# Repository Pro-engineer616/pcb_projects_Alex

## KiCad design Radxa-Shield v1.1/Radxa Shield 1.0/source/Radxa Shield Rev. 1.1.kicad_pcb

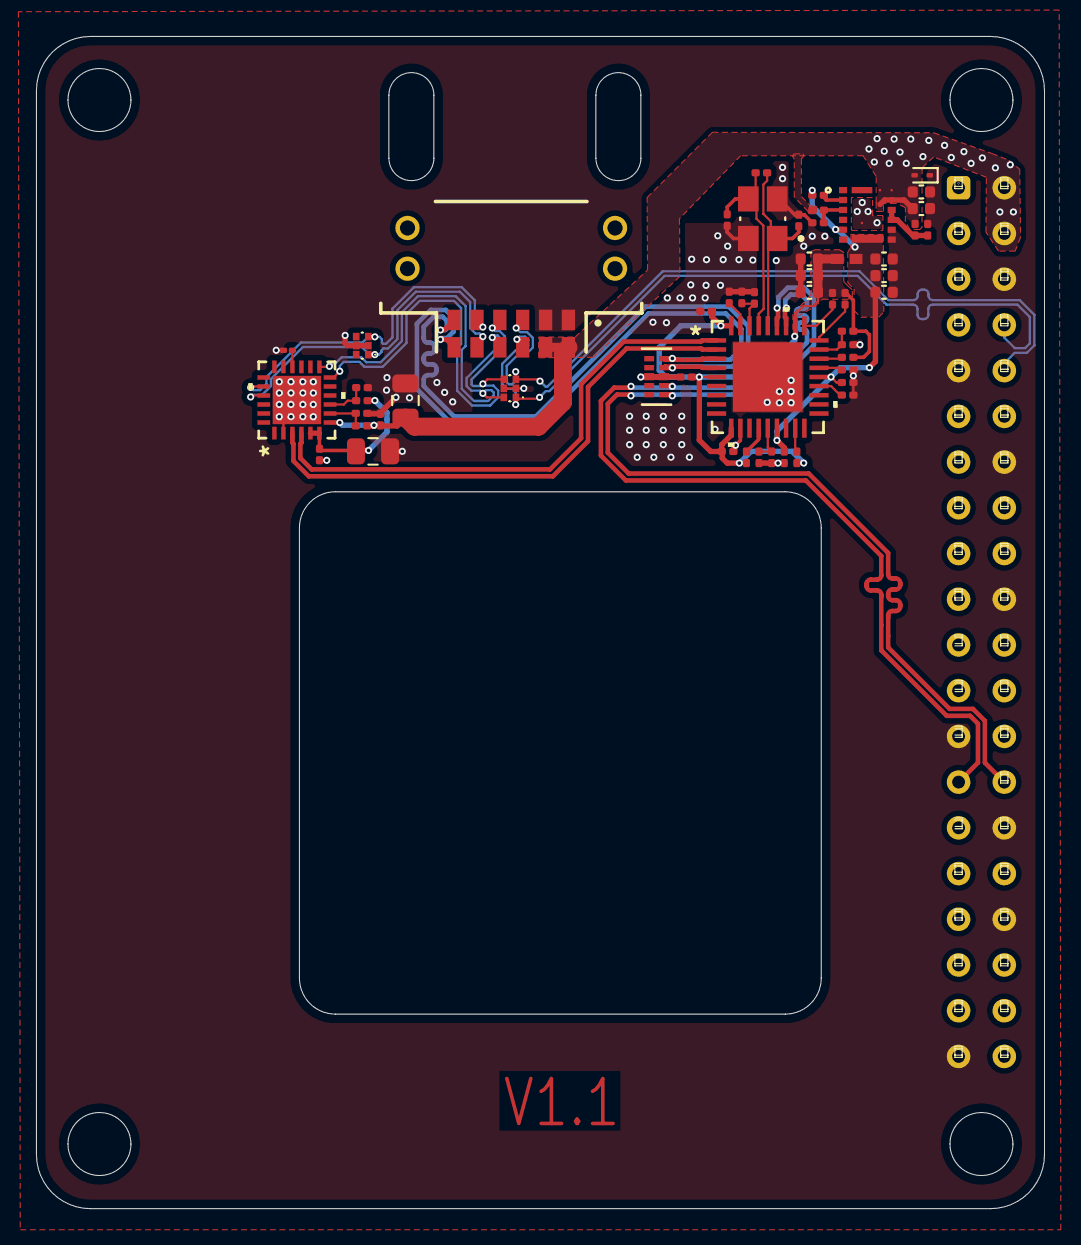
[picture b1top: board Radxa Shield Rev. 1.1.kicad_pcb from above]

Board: 2 copper layers, 56.0 x 65.1 mm, 55 parts (1 on the bottom side), 36 nets.

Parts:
C1, C3, C5, C8, C11, C16, C18, C19, C21, C22, C23: 100n; C_0201_0603Metric
C2, C4: 10u; C_0805_2012Metric
C6: 4.7u; C_01005_0402Metric
C7, C9, C10: 22uF; C_0402_1005Metric
C12, C17: 10nF; C_0201_0603Metric
C13: 220n; C_0201_0603Metric
C14, C15: 18p; C_0201_0603Metric
C24, C25, C26, C27, C28: 10uF; C_0402_1005Metric
D1, D2: PESD3V3L4UF,115; PESD3V3L5UF115
D3: ESD9B5.0ST5G; D_SOD-923
D4: TPD4EUSB30DQAR; DQA10
J1: Conn_02x10_Odd_Even; Samtec_HLE-120-02-xx-DV-TE_2x20_P2.54mm_Horizontal
J2: TFM-106-02-L-DH-TR; SAMTEC_TFM-106-02-L-DH-TR
L1: BLM15BB221SN1D; IND_BLM15_0402_MUR
R1: 24k; R_0201_0603Metric
R2: 47k; R_0201_0603Metric
R3: 4.3k; R_0201_0603Metric
R4, R9, R10, R11, R13, R16, R17: 10k; R_0201_0603Metric
R5: 20k; R_0201_0603Metric
R6: 49.9k; R_0201_0603Metric
R7: 2.7R; R_0201_0603Metric
R8: 12k; R_0201_0603Metric
R12, R14: 100k; R_0201_0603Metric
R15: 1M; R_0201_0603Metric
U1: CP2105-F01-GM; QFN24_4X4_SIL-L
U2: USB2512BI-AEZG; QFN36_6X6MC_MCH
U3: FS1703-3300-AS; P11F1_TDK
Y1: 24MHz; XTAL_TSX-3225_40.0000MF20X-K0

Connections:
+3V3: C7.1, C18.2, C19.2, C24.1, C25.1, L1.2, R6.1, U2.15 (VDD33), U2.23 (VDD33), U3.5 (VOS), U3.7 (VOUT)
+5V: C3.1, C4.1, C9.1, C10.1, D3.2 (A2), J1.2, J1.4, J2.02, J2.04, R1.1, R4.1, R7.1, U1.7 (REGIN), U3.12 (PVIN), U3.13 (PVIN), U3.14 (PVIN), U3.17 (PVIN)
+VDDA33: C21.2, C22.2, C23.2, C26.1, C27.1, C28.1, L1.1, R9.1, R10.1, R11.1, R14.1, R16.2, R17.2, U2.5 (VDDA33), U2.10 (VDDA33), U2.29 (VDDA33), U2.36 (VDDA33)
D+: D4.4 (D2+), J2.11, U2.4 (USBDP_DN2/PRT_DIS_P2)
D-: D4.5 (D2-), J2.12, U2.3 (USBDM_DN2/PRT_DIS_M2)
GND: C1.2, C2.2, C3.2, C4.2, C5.2, C6.2, C7.2, C8.2, C9.2, C10.2, C11.1, C12.1, C13.2, C14.2, C15.2, C16.1, C17.1, C18.1, C19.1, C21.1, C22.1, C23.1, C24.2, C25.2, C26.2, C27.2, C28.2, D1.2 (common_anode_1), D1.5 (common_anode_2), D2.2 (common_anode_1), D2.5 (common_anode_2), D3.1 (A1), D4.3 (GND), D4.8 (GND), J1.6, J1.9, J1.14, J1.20, J1.25, J1.30, J1.34, J1.39, J2.01, J2.03, R2.1, R5.2, R8.2, R12.1, R13.1, U1.2 (GND), U1.25 (EPAD), U2.11 (TEST), U2.37 (EPAD), U3.8 (PGND), U3.9 (AGND), U3.16 (PGND), Y1.2 (GND), Y1.4 (GND__1)
unnamed: C5.1, R3.2, U1.9 (*RST)
unnamed: C6.1, U1.16 (NC/DCD_ECI/VPP)
unnamed: R1.2, R2.2, U1.8 (VBUS)
unnamed: C16.2, C17.2, U2.14 (CRFILT)
unnamed: R11.2, U2.25 (HS_IND/CFG_SEL1)
unnamed: R16.1, U2.13 (OCS_N1)
unnamed: R17.1, U2.17 (OCS_N2)
unnamed: C11.2, C12.2, U2.34 (PLLFILT)
unnamed: R8.1, U2.35 (RBIAS)
unnamed: C13.1, R14.2, U2.26 (RESET_N)
unnamed: R12.2, U2.24 (SCL/SMBCLK/CFG_SEL0)
unnamed: R13.2, U2.22 (SDA/SMBDATA/NON_REM1)
unnamed: R9.2, U2.28 (SUSP_IND/LOCAL_PWR/NON_REM0)
unnamed: R10.2, U2.27 (VBUS_DET)
unnamed: R4.2, R5.1, U3.3 (EN)
unnamed: C8.1, R7.2, U3.10 (VCC), U3.11 (VIN)
PG: R6.2, U3.2 (PG)
UART_RX_ELRS: D1.3 (cathode_(diode_2)), J1.10, J2.05
UART_RX_FC: D1.4 (cathode_(diode_3)), J2.07, U1.12 (RXD_ECI)
UART_RX_HALOW: D2.3 (cathode_(diode_2)), J2.09, U1.20 (RXD_SCI)
UART_TX_ELRS: D1.1 (cathode_(diode_1)), J1.8, J2.06
UART_TX_FC: D1.6 (cathode_(diode_4)), J2.08, U1.13 (TXD_ECI)
UART_TX_HALOW: D2.1 (cathode_(diode_1)), J2.10, U1.21 (TXD_SCI)
USB1_N: U1.4 (D-), U2.1 (USBDM_DN1/PRT_DIS_M1)
USB1_P: U1.3 (D+), U2.2 (USBDP_DN1/PRT_DIS_P1)
USB DN: D4.2 (D1-), J1.27, U2.30 (USBDM_UP)
USB DP: D4.1 (D1+), J1.28, U2.31 (USBDP_UP)
VDD: C1.1, C2.1, R3.1, U1.5 (VIO), U1.6 (VDD)
XTALIN: C15.1, R15.1, U2.33 (XTALIN/CLKIN), Y1.3
XTALOUT: C14.1, R15.2, U2.32 (XTALOUT), Y1.1

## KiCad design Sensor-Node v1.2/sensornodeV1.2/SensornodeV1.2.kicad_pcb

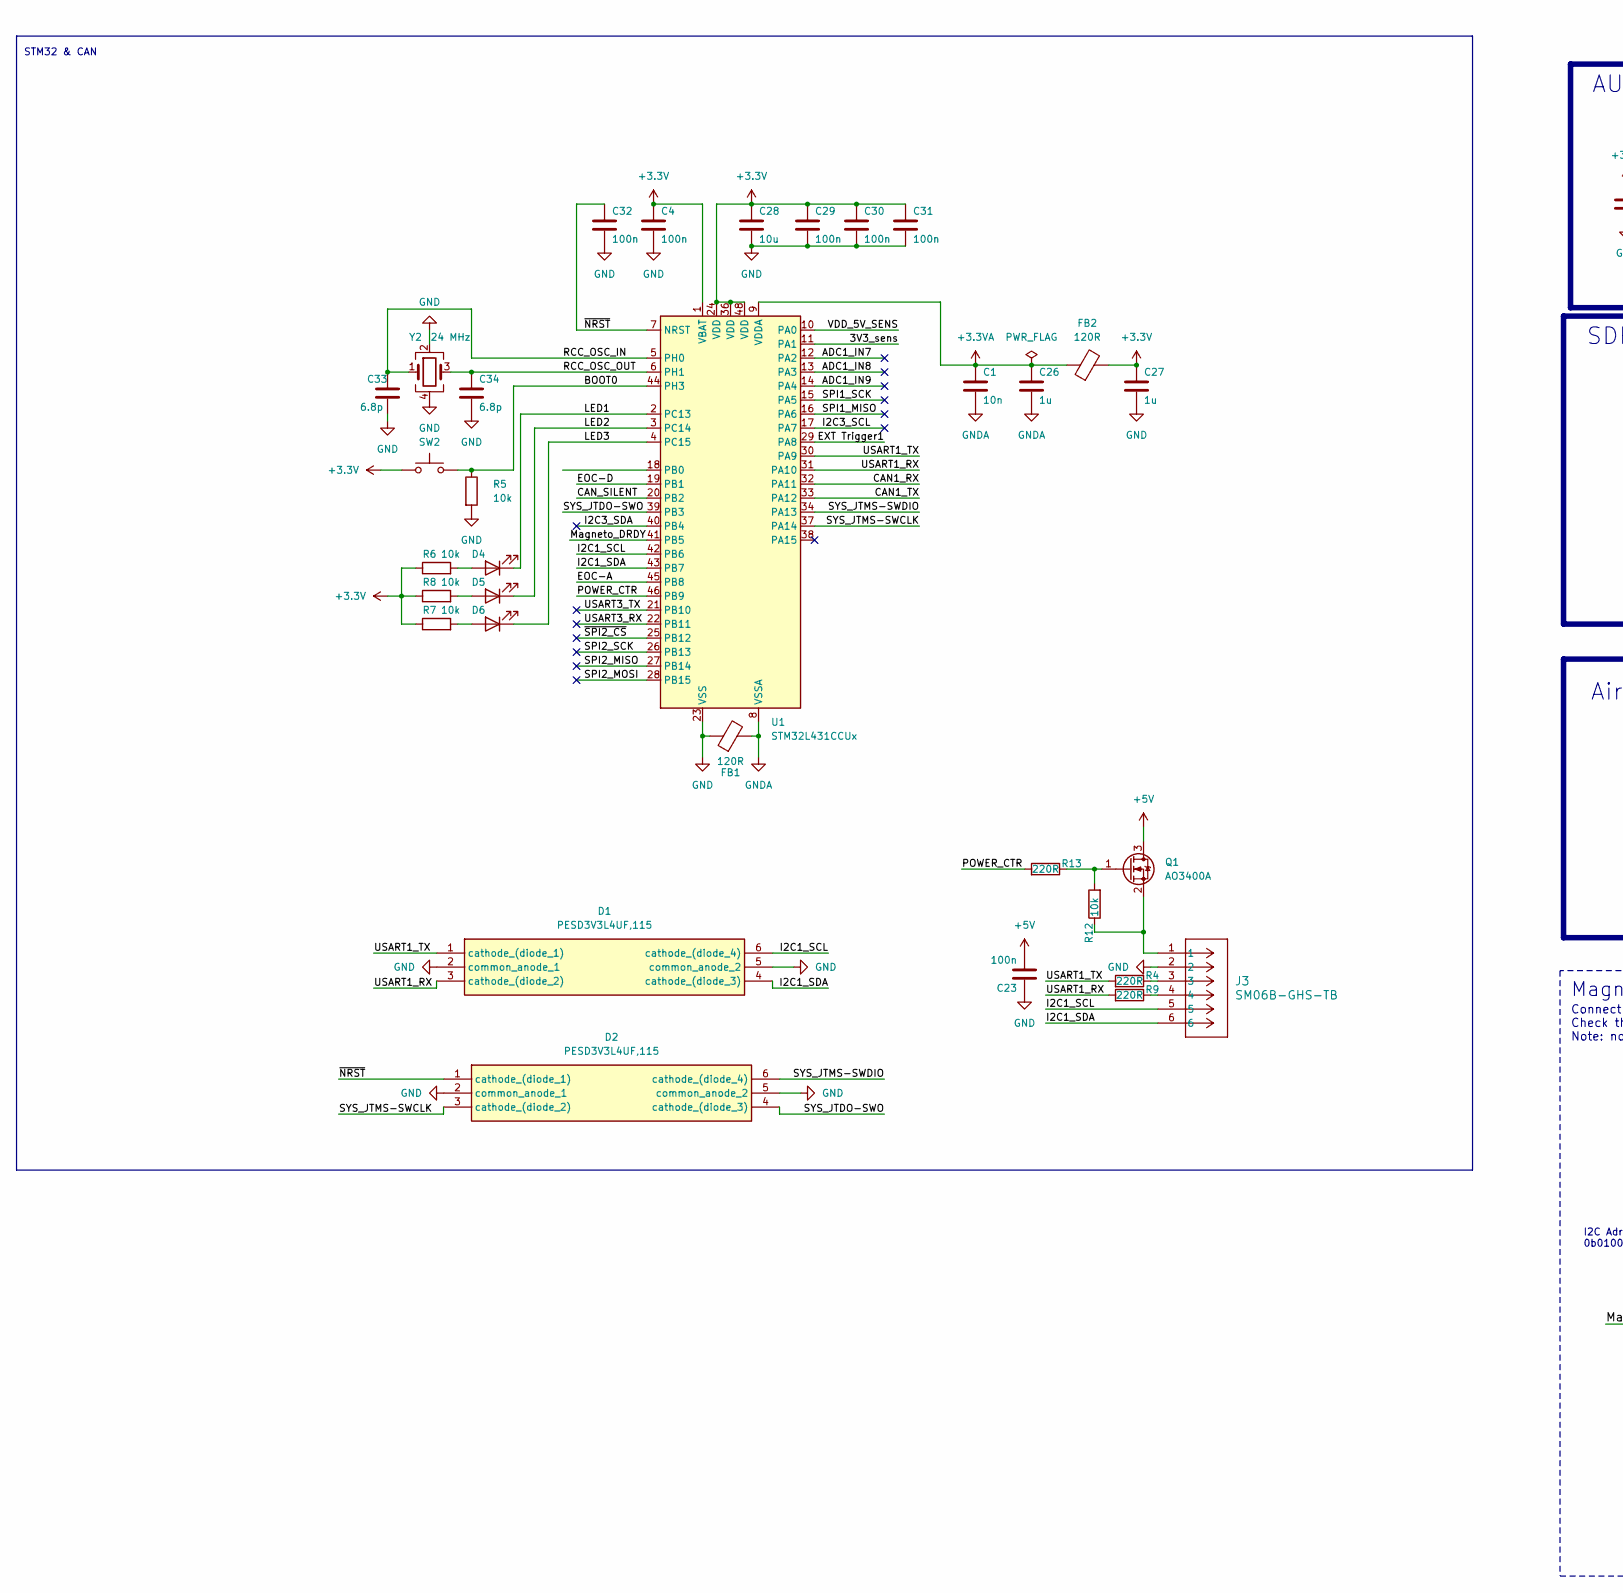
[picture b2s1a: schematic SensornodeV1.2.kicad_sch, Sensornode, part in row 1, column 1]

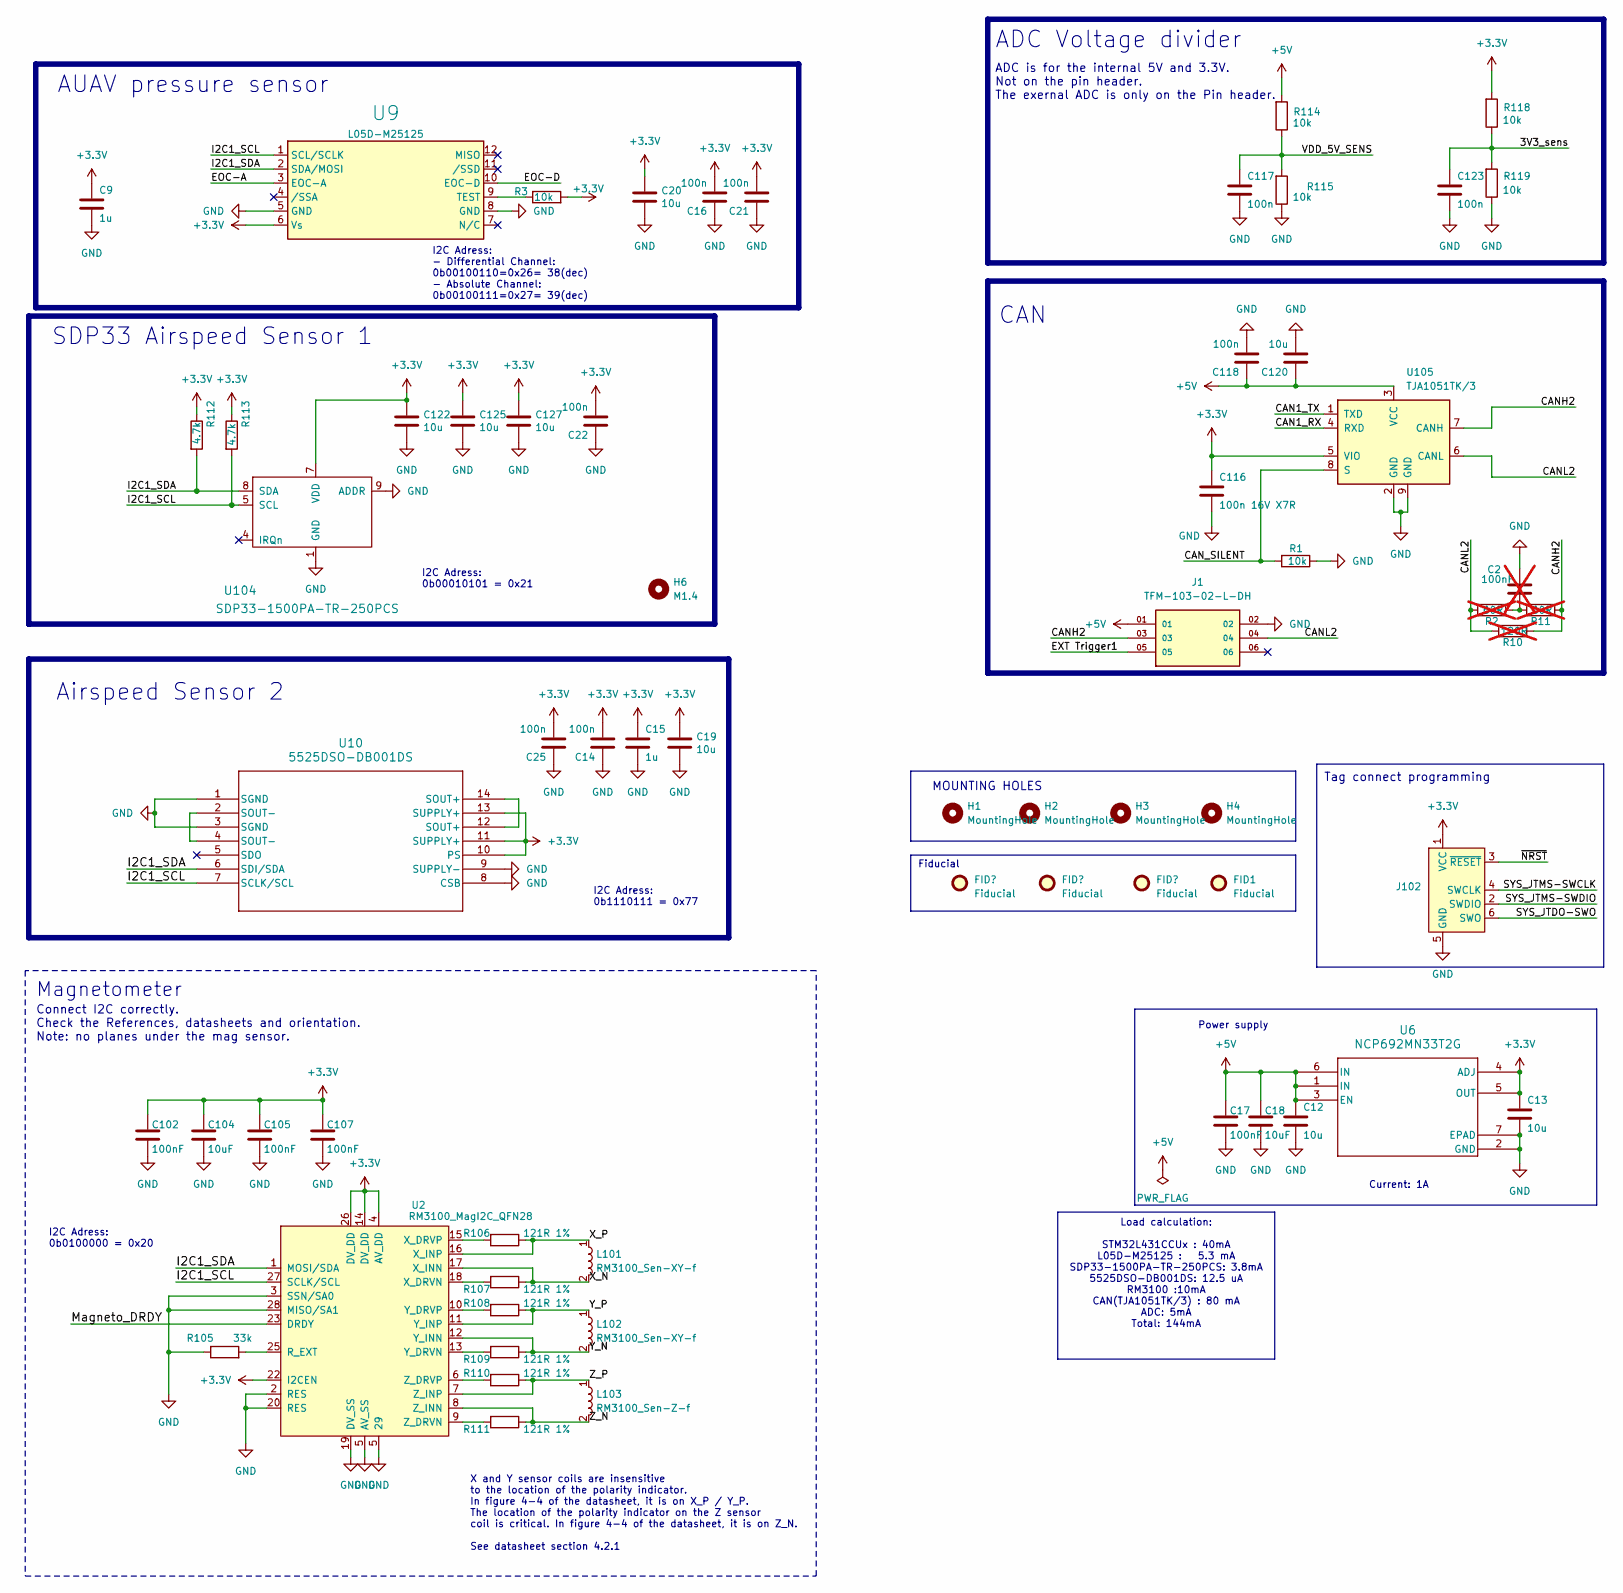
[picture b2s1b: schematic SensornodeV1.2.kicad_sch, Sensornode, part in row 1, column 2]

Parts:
C1: 10n; C_0201_0603Metric; Part GRM033R71A103KA01D
C2: 100nF; R_0201_0603Metric; Part CL05B104KB54PNC; not fitted
C4, C29, C30, C31, C32: 100n; C_0201_0603Metric; Part CL10B104KB8NNWC
C9, C15, C26, C27: 1u; C_0201_0603Metric; Part CL10B105KA8NNNC
C12: 10u; C_1206_3216Metric; Part 1206B106K100NT
C13: 10u; C_0805_2012Metric; Part CL21A106KPFNNNE
C14, C16, C21, C22, C23, C25, C118: 100n; C_0201_0603Metric
C17, C102, C105, C107: 100nF; C_0201_0603Metric; MPN EMF105B7104KVHF
C18, C104: 10uF; C_0402_1005Metric; MPN EMK212BB7106MG-T
C19, C20, C120, C122, C125, C127: 10u; C_0402_1005Metric
C28: 10u; C_0402_1005Metric; Part CL05A106MP5NUNC
C33, C34: 6.8p; C_0201_0603Metric; Part C0201C0G6R8D500NTA
C116: 100n 16V X7R; C_0201_0603Metric; Part GRM033Z71C104KE14D
C117, C123: 100n; C_0201_0603Metric; Part CL21A106KOQNNNE
D1, D2: PESD3V3L4UF,115; PESD3V3L5UF115; Manufacturer_Part_Number PESD3V3L4UF,115; Mouser Part Number 771-PESD3V3L4UFT/R
D4: red; LED_0201_0603Metric; Part XL-0201SURC
D5: green; LED_0201_0603Metric; Part XL-0201UGC
D6: blue; LED_0201_0603Metric; Part XL-0201UBC
FB1, FB2: 120R; C_0201_0603Metric; Part BLM03AG121SN1D
FID1, FID101, FID102, FID103: Fiducial; Fiducial_0.5mm_Mask1.5mm
H1, H2, H3, H4: MountingHole; MountingHole_2.1mm
H6: M1.4; Mounting_Wuerth_WA-SMSI-M1.6_H1.5mm_9774015633
J1: TFM-103-02-L-DH; SAMTEC_TFM-103-02-L-DH; PARTREV F
J3: SM06B-GHS-TB; CONN_SM06B-GHS-TB_JST
J102: Conn_ARM_SWD_TagConnect_TC2030-NL; Tag-Connect_TC2030-IDC-NL_2x03_P1.27mm_Vertical
L101, L102: RM3100_Sen-XY-f; MPN RM3100
L103: RM3100_Sen-Z-f; MPN RM3100
Q1: AO3400A; SOT-23
R1, R114, R115, R118, R119: 10k; R_0201_0603Metric; MPN WR02X1002FAL
R2, R11: 60R; R_0402_1005Metric; PART NUMBER CS02W8J060LTCE; not fitted
R3, R12: 10k; R_0201_0603Metric
R4, R9, R13: 220R; R_0201_0603Metric; MPN RC0201FR-07220RL
R5, R6, R7, R8: 10k; R_0201_0603Metric; Part WR02X1002FAL
R10: 120R; R_0201_0603Metric; PART NUMBER 0402WGF1200TCE; not fitted
R105: 33k; R_0201_0603Metric
R106, R107, R108, R109, R110, R111: 121R 1%; R_0201_0603Metric; MPN RC-01W1210FT
R112, R113: 4.7k; R_0201_0603Metric
SW2: TS-1088R-02026; TS1088R02026
U1: STM32L431CCUx; QFN-48-1EP_7x7mm_P0.5mm_EP5.6x5.6mm
U2: RM3100_MagI2C_QFN28; RM3100_MagI2C_MLF_4x4mm_P0.4; MPN RM3100
U6: NCP692MN33T2G; DFN6_3X3_ONS-L
U9: L05D-M25125; DS-0432
U10: 5525DSO-DB001DS; SO14_MS5525DSO_TEC
U104: SDP33-1500PA-TR-250PCS; SDP3x
U105: TJA1051TK/3; DFN-8-1EP_3x3mm_P0.65mm_EP1.55x2.4mm
Y2: 24 MHz; Crystal_SMD_2016-4Pin_2.0x1.6mm; Part XC21M4-24.000-F06NKDTL

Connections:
+3.3V: C4.1, C9.1, C13.1, C14.2, C15.1, C16.2, C19.1, C20.1, C21.2, C22.2, C25.2, C27.1, C28.1, C29.1, C30.1, C31.1, C102.1, C104.1, C105.1, C107.1, C116.1, C122.1, C125.1, C127.1, FB2.2, J102.1 (VCC), R3.2, R6.1, R7.1, R8.1, R112.1, R113.1, R118.2, SW2.1, U1.1 (VBAT), U1.24 (VDD), U1.36 (VDD), U1.48 (VDD), U2.4 (AV_DD), U2.14 (DV_DD), U2.22 (I2CEN), U2.26 (DV_DD), U6.4 (ADJ), U6.5 (OUT), U9.6 (Vs), U10.10 (PS), U10.11 (SUPPLY+), U10.13 (SUPPLY+), U104.7 (VDD), U105.5 (VIO)
+3.3VA: C1.1, C26.1, FB2.1, U1.9 (VDDA)
+5V: C12.1, C17.1, C18.1, C23.2, C118.1, C120.1, J1.01, Q1.3 (D), R114.2, U6.1 (IN), U6.3 (EN), U6.6 (IN), U105.3 (VCC)
/3V3_sens: C123.1, R118.1, R119.2, U1.11 (PA1)
/ EXT Trigger1: J1.05, U1.29 (PA8)
/ADC1_IN7: U1.12 (PA2)
/ADC1_IN8: U1.13 (PA3)
/ADC1_IN9: U1.14 (PA4)
/BOOT0: R5.1, SW2.2, U1.44 (PH3)
/CAN1_RX: U1.32 (PA11), U105.4 (RXD)
/CAN1_TX: U1.33 (PA12), U105.1 (TXD)
/CANH2: J1.03, R10.1, R11.1, U105.7 (CANH)
/CANL2: J1.04, R2.2, R10.2, U105.6 (CANL)
/CAN_SILENT: R1.2, U1.20 (PB2), U105.8 (S)
/EOC-A: U1.45 (PB8), U9.3 (EOC-A)
/EOC-D: U1.19 (PB1), U9.10 (EOC-D)
/I2C1_SCL: D1.6 (cathode_(diode_4)), J3.5, R113.2, U1.42 (PB6), U2.27 (SCLK/SCL), U9.1 (SCL/SCLK), U10.7 (SCLK/SCL), U104.5 (SCL)
/I2C1_SDA: D1.4 (cathode_(diode_3)), J3.6, R112.2, U1.43 (PB7), U2.1 (MOSI/SDA), U9.2 (SDA/MOSI), U10.6 (SDI/SDA), U104.8 (SDA)
/I2C3_SCL: U1.17 (PA7)
/I2C3_SDA: U1.40 (PB4)
/LED1: D4.1 (K), U1.2 (PC13)
/LED2: D5.1 (K), U1.3 (PC14)
/LED3: D6.1 (K), U1.4 (PC15)
/Magneto_DRDY: U1.41 (PB5), U2.23 (DRDY)
/POWER_CTR: R13.2, U1.46 (PB9)
/RCC_OSC_IN: C33.2, U1.5 (PH0), Y2.1
/RCC_OSC_OUT: C34.2, U1.6 (PH1), Y2.3
/SPI1_MISO: U1.16 (PA6)
/SPI1_SCK: U1.15 (PA5)
/SPI2_MISO: U1.27 (PB14)
/SPI2_MOSI: U1.28 (PB15)
/SPI2_SCK: U1.26 (PB13)
/SYS_JTDO-SWO: D2.4 (cathode_(diode_3)), J102.6 (SWO), U1.39 (PB3)
/SYS_JTMS-SWCLK: D2.3 (cathode_(diode_2)), J102.4 (SWCLK), U1.37 (PA14)
/SYS_JTMS-SWDIO: D2.6 (cathode_(diode_4)), J102.2 (SWDIO), U1.34 (PA13)
/USART1_RX: D1.3 (cathode_(diode_2)), R9.2, U1.31 (PA10)
/USART1_TX: D1.1 (cathode_(diode_1)), R4.2, U1.30 (PA9)
/USART3_RX: U1.22 (PB11)
/USART3_TX: U1.21 (PB10)
/VDD_5V_SENS: C117.1, R114.1, R115.2, U1.10 (PA0)
/X_N: L101.2, R107.1, U2.17 (X_INN)
/X_P: L101.1, R106.1, U2.16 (X_INP)
/Y_N: L102.2, R109.1, U2.12 (Y_INN)
/Y_P: L102.1, R108.1, U2.11 (Y_INP)
/Z_N: L103.2, R111.1, U2.8 (Z_INN)
/Z_P: L103.1, R110.1, U2.7 (Z_INP)
/~NRST: C32.1, D2.1 (cathode_(diode_1)), J102.3 (~RESET), U1.7 (NRST)
/~SPI2_CS: U1.25 (PB12)
GND: C2.2, C4.2, C9.2, C12.2, C13.2, C14.1, C15.2, C16.1, C17.2, C18.2, C19.2, C20.2, C21.1, C22.1, C23.1, C25.1, C27.2, C28.2, C29.2, C30.2, C31.2, C32.2, C33.1, C34.1, C102.2, C104.2, C105.2, C107.2, C116.2, C117.2, C118.2, C120.2, C122.2, C123.2, C125.2, C127.2, D1.2 (common_anode_1), D1.5 (common_anode_2), D2.2 (common_anode_1), D2.5 (common_anode_2), FB1.1, J1.02, J3.2, J102.5 (GND), R1.1, R5.2, R105.1, R115.1, R119.1, U1.23 (VSS), U1.35 (VSS), U1.47 (VSS), U1.49 (VSS), U2.2 (RES), U2.3 (SSN/SA0), U2.5 (29), U2.19 (DV_SS), U2.20 (RES), U2.28 (MISO/SA1), U2.29, U6.2 (GND), U6.7 (EPAD), U9.5 (GND), U9.8 (GND), U10.1 (SGND), U10.3 (SGND), U10.8 (CSB), U10.9 (SUPPLY-), U104.1 (GND), U104.2 (GND), U104.3 (GND), U104.6 (GND), U104.9 (ADDR), U104.10 (GND), U104.11 (GND), U104.17 (GND), U104.18 (GND), U105.2 (GND), U105.9 (GND), Y2.2, Y2.4
GNDA: C1.2, C26.2, FB1.2, U1.8 (VSSA)
unnamed: C2.1, R2.1, R11.2
unnamed: D4.2 (A), R6.2
unnamed: D5.2 (A), R7.2
unnamed: D6.2 (A), R8.2
unnamed: J3.3, R4.1
unnamed: J3.4, R9.1
unnamed: Q1.1 (G), R12.2, R13.1
unnamed: J3.1, Q1.2 (S), R12.1
unnamed: R105.2, U2.25 (R_EXT)
unnamed: R107.2, U2.18 (X_DRVN)
unnamed: R106.2, U2.15 (X_DRVP)
unnamed: R109.2, U2.13 (Y_DRVN)
unnamed: R108.2, U2.10 (Y_DRVP)
unnamed: R111.2, U2.9 (Z_DRVN)
unnamed: R110.2, U2.6 (Z_DRVP)
unnamed: R3.1, U9.9 (TEST)
unnamed: U10.12 (SOUT+), U10.14 (SOUT+)
unnamed: U10.2 (SOUT-), U10.4 (SOUT-)

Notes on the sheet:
Load calculation: STM32L431CCUx : 40mA L05D-M25125 : 5.3 mA SDP33-1500PA-TR-250PCS: 3.8mA 5525DSO-DB001DS: 12.5 uA RM3100 :10mA CAN(TJA1051TK/3) : 80 mA ADC: 5mA Total: 144mA
STM32 & CAN
I2C Adress: 0b0100000 = 0x20
SDP33 Airspeed Sensor 1
Power supply
Fiducial
Connect I2C correctly. Check the References, datasheets and orientation. Note: no planes under the mag sensor.
ADC Voltage divider
MOUNTING HOLES
I2C Adress: 0b00010101 = 0x21
ADC is for the internal 5V and 3.3V. Not on the pin header. The exernal ADC is only on the Pin header.
CAN
I2C Adress: - Differential Channel: 0b00100110=0x26= 38(dec) - Absolute Channel: 0b00100111=0x27= 39(dec)
I2C Adress: 0b1110111 = 0x77
Magnetometer
X and Y sensor coils are insensitive to the location of the polarity indicator. In figure 4-4 of the datasheet, it is on X_P / Y_P. The location of the polarity indicator on the Z sensor coil is critical. In figure 4-4 of the datasheet, it is on Z_N. See datasheet section 4.2.1
Airspeed Sensor 2
AUAV pressure sensor
Tag connect programming
Current: 1A

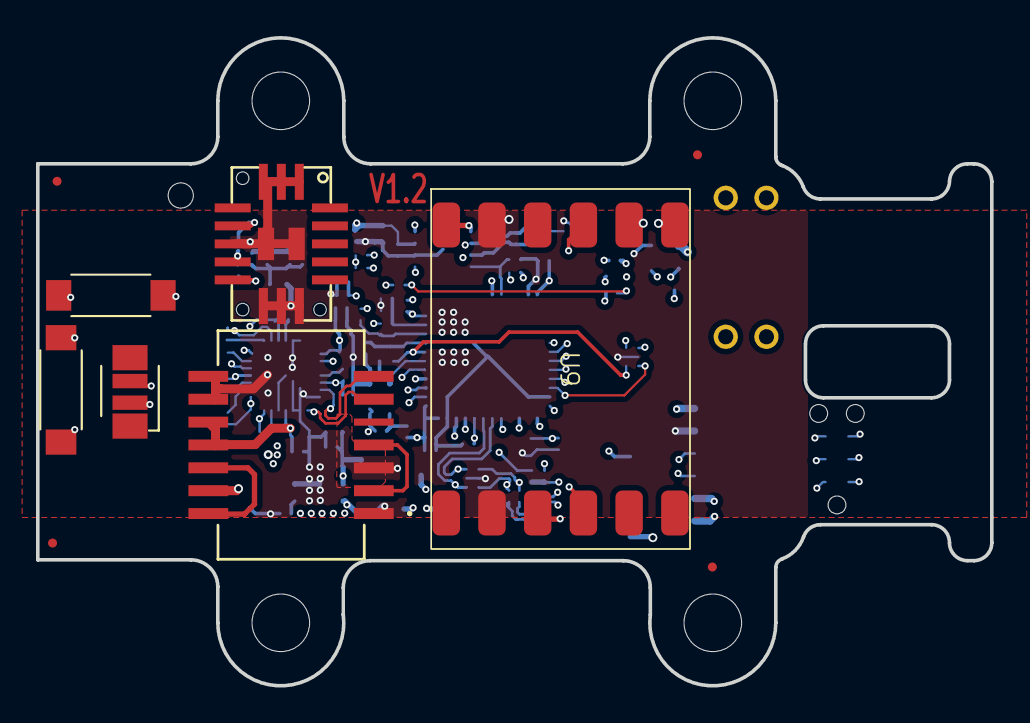
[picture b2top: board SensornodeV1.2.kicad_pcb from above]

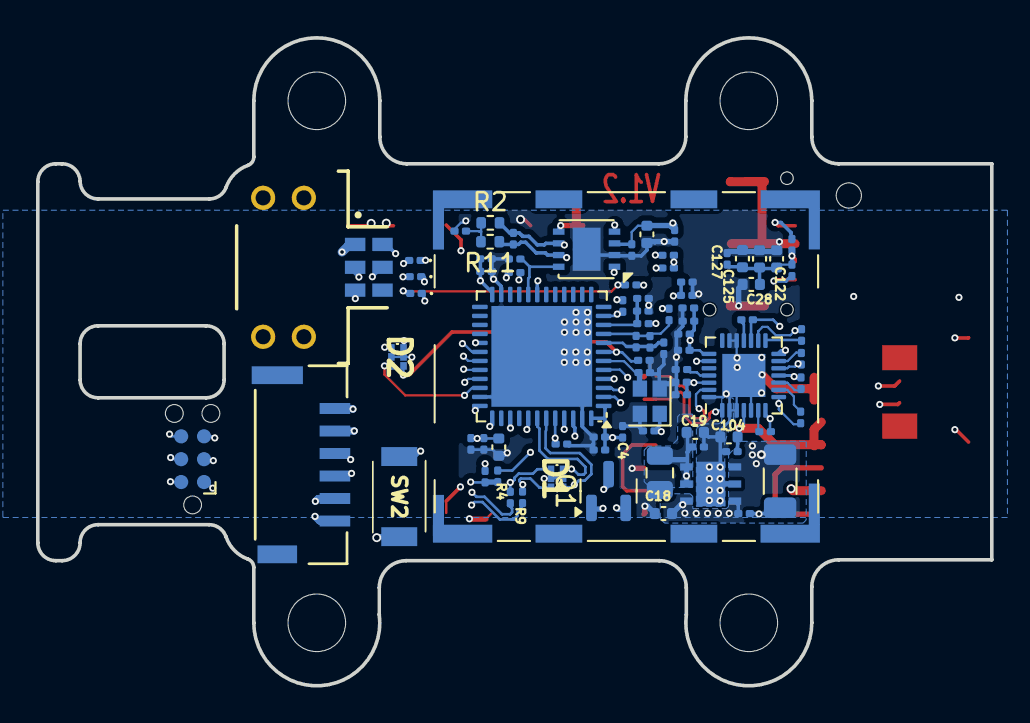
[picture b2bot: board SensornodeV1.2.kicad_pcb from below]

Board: 6 copper layers, 53.0 x 36.0 mm, 97 parts (86 on the bottom side), 55 nets.

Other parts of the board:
J2: Conn_01x01_Shielded; Wuerth_36103205_20x20mm

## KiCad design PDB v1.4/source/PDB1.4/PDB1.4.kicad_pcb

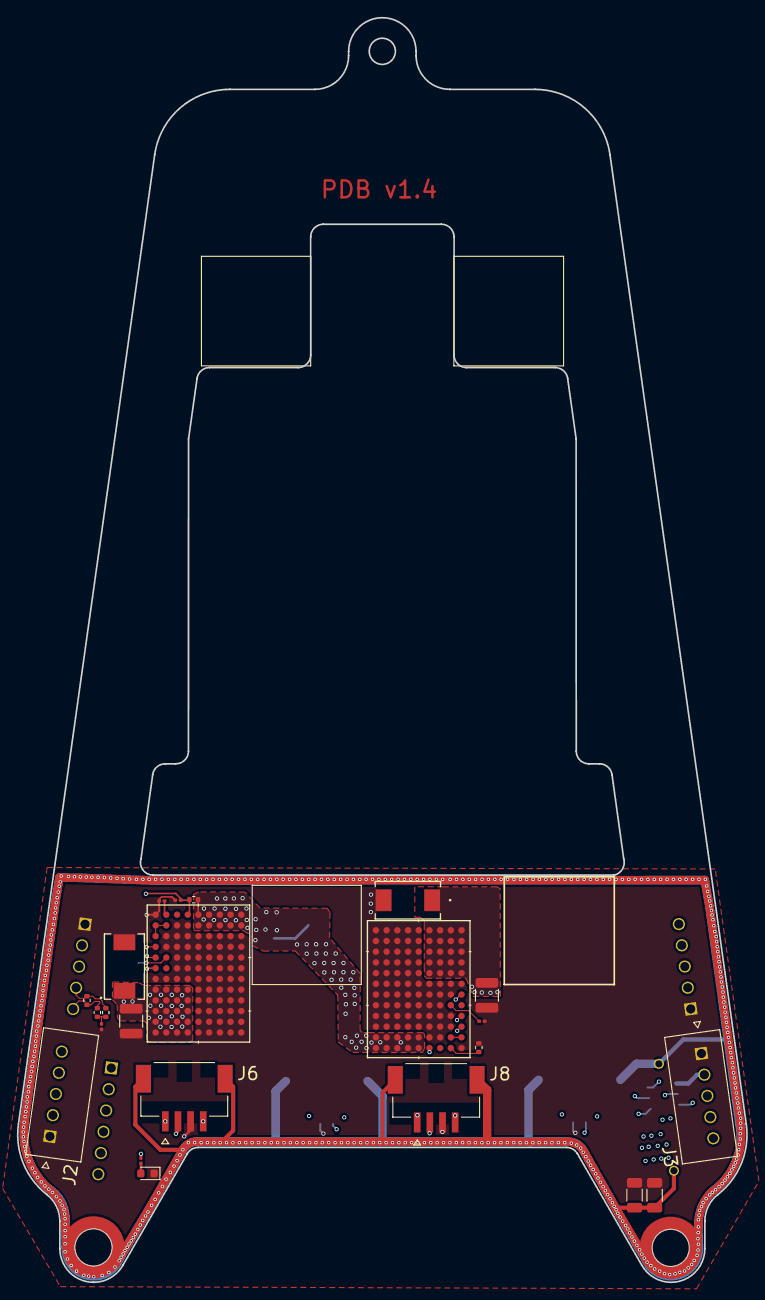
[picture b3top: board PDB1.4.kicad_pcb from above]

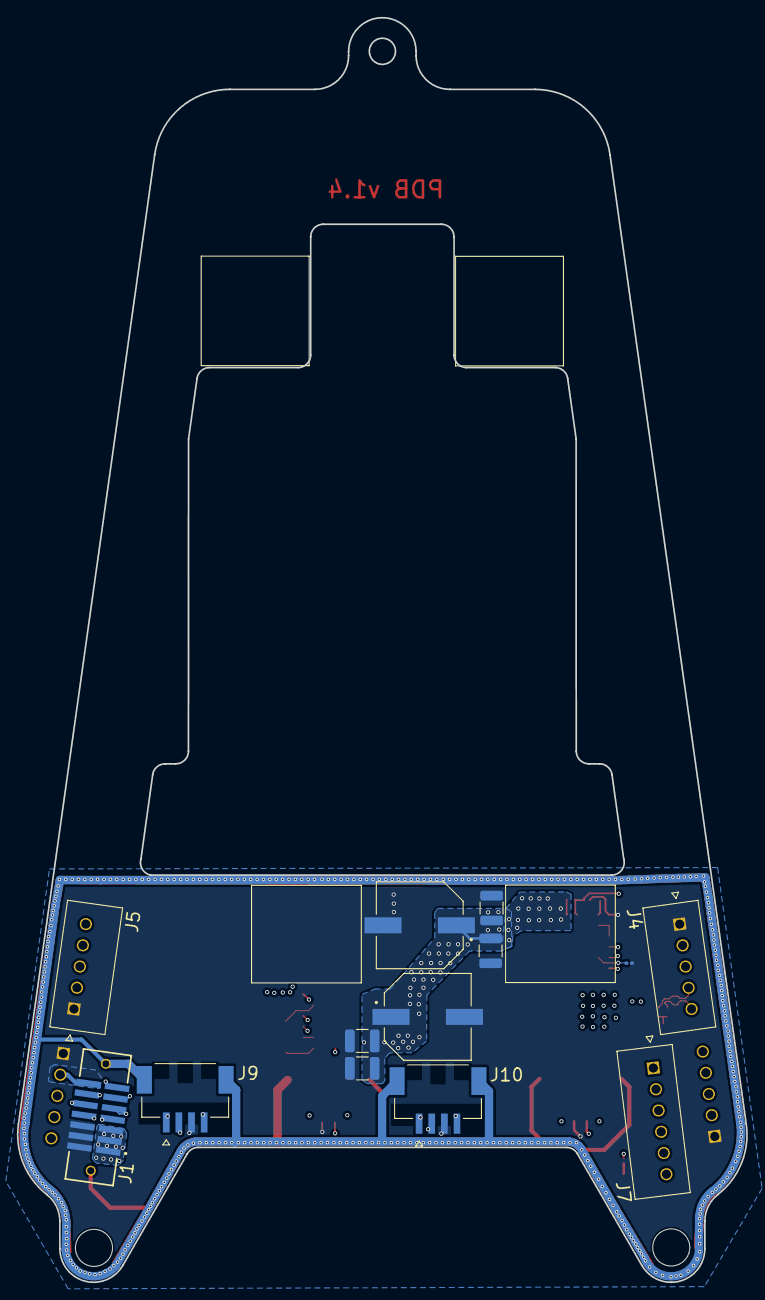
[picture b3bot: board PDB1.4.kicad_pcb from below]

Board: 6 copper layers, 86.5 x 150.0 mm, 38 parts (13 on the bottom side), 23 nets.

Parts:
C1, C6: 15uf; CAP_100SXV15MX
C2, C3, C7, C8: 10u; C_1210_3225Metric
C4, C9: 150uF; CAP_TRM-E-2917_AVX-L
C5, C10: 100uF; C_1210_3225Metric
C12: 470pF; C_1206_3216Metric
C17: 100nF; C_0201_0603Metric
D1: NCD0603C1; LED_0603_1608Metric
J1: TFM-107-02-L-D-WT; SAMTEC_TFM-107-02-L-D-WT
J2, J3, J4, J5: 1719710105; MOLEX_1719710105
J6, J8, J9, J10: 2132250430; MOLEX_2132250430
J7: 1719710106; MOLEX_1719710106
MP1, MP2: WA-SMSI_9774XXX360; WA-SMSI_9774120360
R1, R2, R5: 124k; R_0201_0603Metric
R3: 374k; R_0402_1005Metric
R4: 2.87k; R_0201_0603Metric
R6, R10: 60R; R_0402_1005Metric
R7: 2.8k; R_0402_1005Metric
R8: 100k; R_0201_0603Metric
R9: 120R; R_0402_1005Metric
R17: 2M; C_1206_3216Metric
U1, U2: LTM8064IY#PBF; BGA108_16X11P9_ADI

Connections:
+8V: C4.1, C5.2, C9.1, C10.2, J1.14, J2.2, J3.2, J4.2, J5.2, J7.5, R8.2, U1.H1 (VOUT), U1.H2 (VOUT), U1.H3 (VOUT), U1.H4 (VOUT), U1.J1 (VOUT), U1.J2 (VOUT), U1.J3 (VOUT), U1.J4 (VOUT), U1.K1 (VOUT), U1.K2 (VOUT), U1.K3 (VOUT), U1.K4 (VOUT), U1.L1 (VOUT), U1.L2 (VOUT), U1.L3 (VOUT), U1.L4 (VOUT), U1.M1 (VOUT), U1.M2 (VOUT), U1.M3 (VOUT), U1.M4 (VOUT), U2.H1 (VOUT), U2.H2 (VOUT), U2.H3 (VOUT), U2.H4 (VOUT), U2.J1 (VOUT), U2.J2 (VOUT), U2.J3 (VOUT), U2.J4 (VOUT), U2.K1 (VOUT), U2.K2 (VOUT), U2.K3 (VOUT), U2.K4 (VOUT), U2.L1 (VOUT), U2.L2 (VOUT), U2.L3 (VOUT), U2.L4 (VOUT), U2.M1 (VOUT), U2.M2 (VOUT), U2.M3 (VOUT), U2.M4 (VOUT)
/power/IOUTMON: U1.E1 (IOUTMON), U2.C1 (CTRL1)
/power/PWR_RUN: R2.2, R3.1, U1.A4 (RUN), U2.A4 (RUN)
/power/PWR_SS: U1.D1 (SS), U2.D1 (SS)
/power/SYNC: U1.F1 (SYNC), U2.F1 (SYNC)
CAN H1: J1.07, J2.5, J3.5, J4.5, J5.5, J6.4, J7.3, J8.4, J9.4, J10.4, R9.1, R10.1
CAN L1: J1.08, J2.4, J3.4, J4.4, J5.4, J6.1, J7.4, J8.1, J9.1, J10.1, R6.2, R9.2
Detach: J1.09, J7.2
GND: C1.2, C2.2, C3.2, C4.2, C5.1, C6.2, C7.2, C8.2, C9.2, C10.1, C12.2, C17.2, D1.1 (K), J1.02, J1.04, J1.06, J2.1, J3.1, J4.1, J5.1, J6.3, J8.3, J9.3, J10.3, R1.1, R2.1, R4.2, R5.1, R7.2, R17.2, U1.A1 (GND), U1.B3 (GND), U1.B4 (GND), U1.C2 (GND), U1.C3 (GND), U1.C4 (GND), U1.C5 (GND), U1.C6 (GND), U1.C7 (GND), U1.C8 (GND), U1.C9 (GND), U1.D2 (GND), U1.D3 (GND), U1.D4 (GND), U1.D5 (GND), U1.D6 (GND), U1.D7 (GND), U1.D8 (GND), U1.D9 (GND), U1.E3 (GND), U1.E4 (GND), U1.E5 (GND), U1.E6 (GND), U1.E7 (GND), U1.E8 (GND), U1.E9 (GND), U1.F3 (GND), U1.F4 (GND), U1.F5 (GND), U1.F6 (GND), U1.F7 (GND), U1.F8 (GND), U1.F9 (GND), U1.G1 (GND), U1.G2 (GND), U1.G3 (GND), U1.G4 (GND), U1.G5 (GND), U1.G6 (GND), U1.G7 (GND), U1.G8 (GND), U1.G9 (GND), U1.H5 (GND), U1.H6 (GND), U1.H7 (GND), U1.H8 (GND), U1.H9 (GND), U1.J5 (GND), U1.J6 (GND), U1.J7 (GND), U1.J8 (GND), U1.J9 (GND), U1.K5 (GND), U1.K6 (GND), U1.K7 (GND), U1.K8 (GND), U1.K9 (GND), U1.L5 (GND), U1.L6 (GND), U1.L7 (GND), U1.L8 (GND), U1.L9 (GND), U1.M5 (GND), U1.M6 (GND), U1.M7 (GND), U1.M8 (GND), U1.M9 (GND), U2.A1 (GND), U2.B3 (GND), U2.B4 (GND), U2.C2 (GND), U2.C3 (GND), U2.C4 (GND), U2.C5 (GND), U2.C6 (GND), U2.C7 (GND), U2.C8 (GND), U2.C9 (GND), U2.D2 (GND), U2.D3 (GND), U2.D4 (GND), U2.D5 (GND), U2.D6 (GND), U2.D7 (GND), U2.D8 (GND), U2.D9 (GND), U2.E3 (GND), U2.E4 (GND), U2.E5 (GND), U2.E6 (GND), U2.E7 (GND), U2.E8 (GND), U2.E9 (GND), U2.F2 (MODE), U2.F3 (GND), U2.F4 (GND), U2.F5 (GND), U2.F6 (GND), U2.F7 (GND), U2.F8 (GND), U2.F9 (GND), U2.G1 (GND), U2.G2 (GND), U2.G3 (GND), U2.G4 (GND), U2.G5 (GND), U2.G6 (GND), U2.G7 (GND), U2.G8 (GND), U2.G9 (GND), U2.H5 (GND), U2.H6 (GND), U2.H7 (GND), U2.H8 (GND), U2.H9 (GND), U2.J5 (GND), U2.J6 (GND), U2.J7 (GND), U2.J8 (GND), U2.J9 (GND), U2.K5 (GND), U2.K6 (GND), U2.K7 (GND), U2.K8 (GND), U2.K9 (GND), U2.L5 (GND), U2.L6 (GND), U2.L7 (GND), U2.L8 (GND), U2.L9 (GND), U2.M5 (GND), U2.M6 (GND), U2.M7 (GND), U2.M8 (GND), U2.M9 (GND)
GND_Shield: C12.1, J1.S1, J1.S2, J6.S1 (SHIELD1), J6.S2 (SHIELD2), J8.S1 (SHIELD1), J8.S2 (SHIELD2), J9.S1 (SHIELD1), J9.S2 (SHIELD2), J10.S1 (SHIELD1), J10.S2 (SHIELD2), MP1.1, MP2.1, R17.1
unnamed: C17.1, R6.1, R10.2
unnamed: D1.2 (A), R8.1
unnamed: U1.B1 (CTRL2), U1.B2 (VREF), U1.C1 (CTRL1)
unnamed: R4.1, U1.A2 (FB)
unnamed: R1.2, U1.E2 (RT)
unnamed: U2.B1 (CTRL2), U2.B2 (VREF)
unnamed: R7.1, U2.A2 (FB)
unnamed: R5.2, U2.E2 (RT)
PWM1: J1.11, J5.3
PWM2: J1.10, J4.3
PWM3: J1.13, J3.3
PWM4: J1.12, J2.3
VBAT: C1.1, C2.1, C3.1, C6.1, C7.1, C8.1, J1.01, J1.03, J1.05, J6.2, J8.2, J9.2, J10.2, R3.2, U1.A5 (VIN), U1.A6 (VIN), U1.A7 (VIN), U1.A8 (VIN), U1.A9 (VIN), U1.B5 (VIN), U1.B6 (VIN), U1.B7 (VIN), U1.B8 (VIN), U1.B9 (VIN), U2.A5 (VIN), U2.A6 (VIN), U2.A7 (VIN), U2.A8 (VIN), U2.A9 (VIN), U2.B5 (VIN), U2.B6 (VIN), U2.B7 (VIN), U2.B8 (VIN), U2.B9 (VIN)
